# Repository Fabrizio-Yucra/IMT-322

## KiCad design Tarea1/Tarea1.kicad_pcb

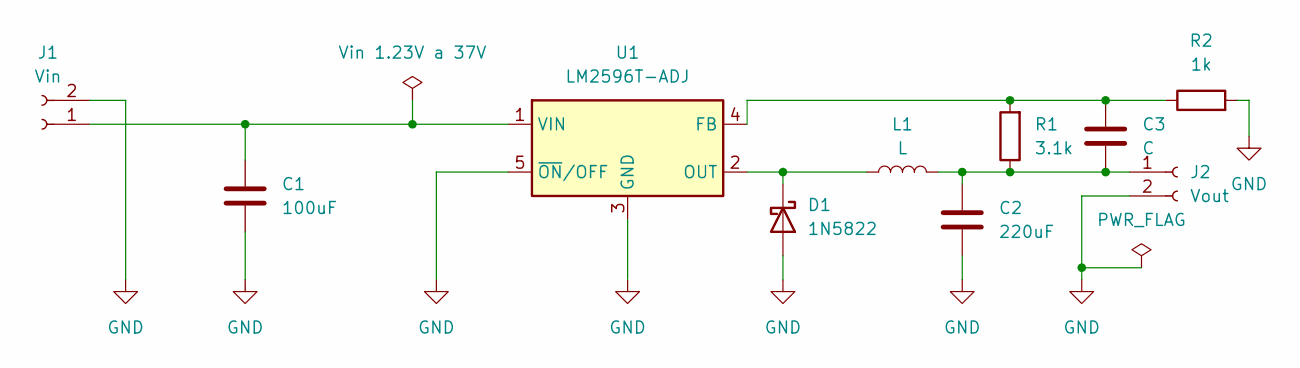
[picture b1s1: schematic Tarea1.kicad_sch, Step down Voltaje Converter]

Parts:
C1: 100uF; C_1210_3225Metric
C2: 220uF; C_1210_3225Metric
C3: C; C_1210_3225Metric
D1: 1N5822; D_DO-201AD_P5.08mm_Vertical_KathodeUp
J1: Vin; SolderWire-1.5sqmm_1x02_P6mm_D1.7mm_OD3mm
J2: Vout; SolderWire-1.5sqmm_1x02_P6mm_D1.7mm_OD3mm
L1: L; L_Cenker_CKCS8080
R1: 3.1k; R_0805_2012Metric
R2: 1k; R_0805_2012Metric
U1: LM2596T-ADJ; TO-220-5_P3.4x3.7mm_StaggerOdd_Lead3.8mm_Vertical

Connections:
GND: C1.2, C2.2, D1.2 (A), J1.2, J2.2, R2.2, U1.3 (GND), U1.5 (~ON/OFF)
unnamed: D1.1 (K), L1.1, U1.2 (OUT)
unnamed: C1.1, J1.1, U1.1 (VIN)
unnamed: C2.1, C3.2, J2.1, L1.2, R1.1
unnamed: C3.1, R1.2, R2.1, U1.4 (FB)

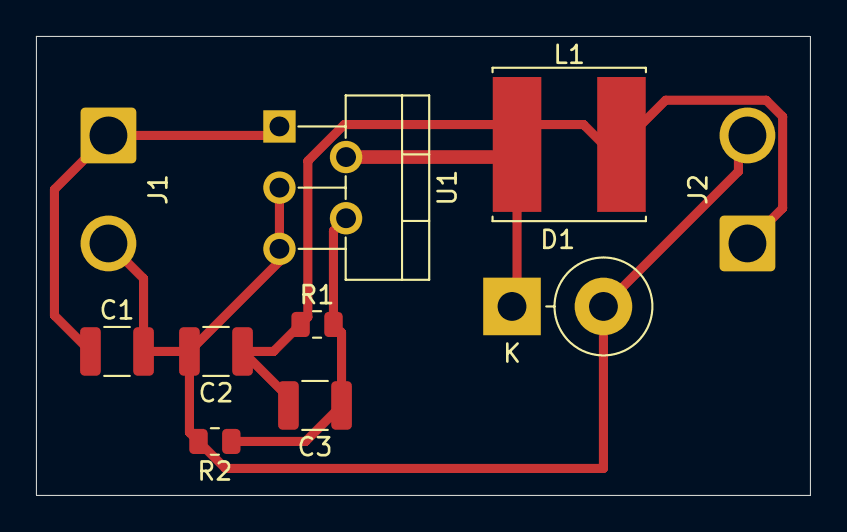
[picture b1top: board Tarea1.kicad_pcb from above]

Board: 2 copper layers, 43.0 x 25.5 mm, 10 parts (0 on the bottom side), 5 nets.

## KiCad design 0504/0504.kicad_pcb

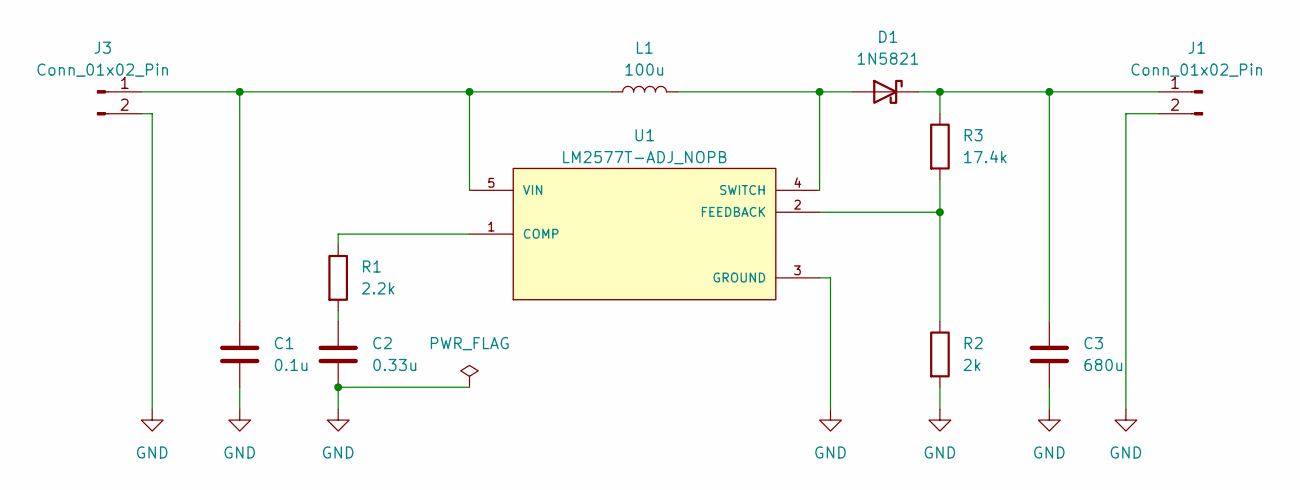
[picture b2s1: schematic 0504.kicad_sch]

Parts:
C1: 0.1u; C_1206_3216Metric
C2: 0.33u; C_1206_3216Metric_Pad1.33x1.80mm_HandSolder
C3: 680u; C_1206_3216Metric
D1: 1N5821; D_DO-201AD_P15.24mm_Horizontal
J1, J3: Conn_01x02_Pin; SolderWire-0.5sqmm_1x02_P4.6mm_D0.9mm_OD2.1mm
L1: 100u; L_1210_3225Metric_Pad1.42x2.65mm_HandSolder
R1: 2.2k; R_MELF_MMB-0207
R2: 2k; R_MELF_MMB-0207
R3: 17.4k; R_MELF_MMB-0207
U1: LM2577T-ADJ_NOPB; VREG_LM2577T-ADJ_NOPB; PARTREV D

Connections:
GND: C1.2, C2.2, C3.2, J1.2, J3.2, R2.2, U1.3 (GROUND)
unnamed: C2.1, R1.2
unnamed: D1.2 (A), L1.2, U1.4 (SWITCH)
unnamed: C3.1, D1.1 (K), J1.1, R3.1
unnamed: C1.1, J3.1, L1.1, U1.5 (VIN)
unnamed: R1.1, U1.1 (COMP)
unnamed: R2.1, R3.2, U1.2 (FEEDBACK)

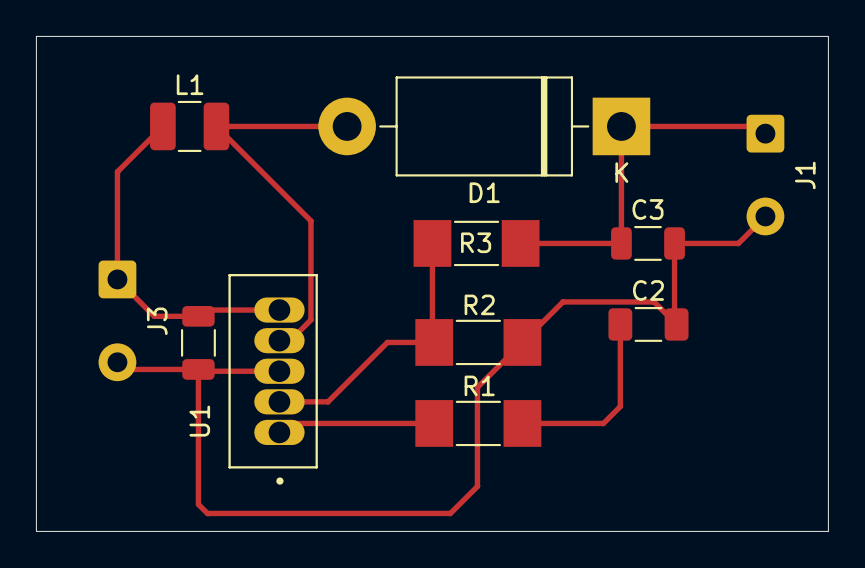
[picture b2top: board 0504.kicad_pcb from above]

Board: 2 copper layers, 44.0 x 27.5 mm, 11 parts (0 on the bottom side), 7 nets.

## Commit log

2024-02-17 readme Fabri
2024-02-17 denuevo
2024-02-17 primer codigo
2024-02-24 Ejercicio1
2024-02-24 Ejercicios en Clase
2024-03-02 Pracctica2
2024-03-09 Práctica 3
2024-03-19 EXAMEN 19_03
2024-03-19 PRACTICA 4
2024-04-12 Ejercicio de clase sobre como hacer una PCB
2024-04-12 Ejercicio de PCB
2024-04-13 Version cambiada y corregida
2024-04-20 Practica de Semaforo
2024-04-20 Ejercicio de muestreo de datos
2024-04-22 Diseño de PCB sobre un conversor reductor
2024-04-22 Diseño PCB de convertidor reductor de voltaje
2024-04-23 Ascensor de 3 pisos
2024-04-25 Ascensor con interfaz
2024-04-27 Examen2 Sistemas embebidos Maquina expendedora de bebidas
2024-04-27 Examen Maquina expendedora de bebidas
2024-05-21 Ejercicio Raspberry
2024-05-23 Examen recuperatorio
2024-05-28 Examen Raspberry
2024-05-28 Examen rasp
